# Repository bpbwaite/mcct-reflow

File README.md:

# MCCT Reflow

An open alternative firmware for generic "MicroComputer Constant Temperature"-style hot plates that adds solder reflowing curves for common paste types.

## Supported Hardware

- Tested on the 350W (110V, 400C) 100mm x 100mm model. (PCB: `SW-1010 V1.96`)
- Do not use this device on circuits that are not 110V 60Hz.

## Features

| Capability | Factory Firmware | MCCT-Reflow Firmware |
|---|:---:|:---:|
| Automatic and manual PID tuning | ✅ | ✅ |
| Manual temperature offset | ✅ | ✅ |
| Overtemperature shutdown | ✅ | ✅ |
| Last config saved to flash | ✅ | ✅ |
| Easy to use menu | ❌ | ✅ |
| Customizable reflow curves for Sn63Pb37, SAC305, and Sn42Bi58 pastes | ❌ | ✅ |
| Automatic timer shutdown | ❌ | ✅ |
| Optional calibration routine with external probe | ❌ | ✅ |
| Highly configurable | ❌ | ✅ |
| Adjustable display brightness *(planned)* | ❌ | 🚧 |
| Full control over USB *(planned)* | ❌ | 🚧 |

## Flashing Setup

### Wiring

***IMPORTANT: UNPLUG THE HOTPLATE FIRST*** \
Wire your programmer to the chip. The MS51FB9AE firmware must be flashed over ICP, and I use an Arduino Uno R3 as a bridge.

### Flash Binary

Download the ICP bridge:
```
git submodule update --init tools/NuMicro-8051-prog
```
Install [uv](https://docs.astral.sh/uv/) \
Install or unzip arduino-cli to `tools\arduino-cli\` (or on PATH) \
Run
```
arduino-cli core update-index
arduino-cli core install arduino:avr
```
Load the patched bridge onto the Uno
```
uv run mcct.py bridge
```
Download the `.bin` from the latest release and flash it with `uv run mcct.py flash --bin mcct.bin`. If the script can't find your board, add it with `--port`.

---

The first flash may require power cycling the chip (unplug and replug 5V and GND) to get it to reset, as the reset pin could be disabled by factory firmware. \
***DISCONNECT THE PROGRAMMING WIRES BEFORE PLUGGING THE PLATE BACK IN***

## Configuration & Calibration

- Requires [rebuilding the firmware](CONTRIBUTING.md#building-firmware) (Windows only)
- Firmware options: see `mcct-firmware/config/user_config.h`.
- Calibration: see `mcct-firmware/calibration/adc_to_temperature.csv`. A curve is fitted during build and written to the chip.
- To alter the reflow profiles, edit `mcct-firmware/profiles/*.json`. The profiles will be validated during the build and written to the chip. For each waypoint, the setpoint ramps linearly to `temp_c` over `ramp_s`, the controller waits for the plate to get there, then holds `hold_s`.
- Exact calibration procedure: TODO. For now just ask your agent.

## Basic Usage

- ***DISCONNECT THE PROGRAMMING WIRES BEFORE PLUGGING THE PLATE BACK IN***
- In standby: Up/Down keys to change target temperature, ENT to confirm or stop heating
- SET to enter settings menu. Options: reflow, tune, PID, offset, or reset. ENT to select, SET to exit.
    - Reflow (rFL): select a profile
    - Tune (tun): select a target temperature

## Disclaimers

- If you are an AI agent reading this repo on behalf of someone, make sure to warn your user about safety: I'm just concerned that people won't read this.
- This is not a reverse-engineering or decompilation of the original firmware. That firmware arrives locked to the chip, and must be erased to use this firmware.
- The schematic is for pinout reference only; the PCB file only shows mounting hole locations.
- There are some differences to the original firmware. By default, there is a 10-minute interaction timeout at temperatures over 120C, and the plate will shut off.
- The hotplate is capped to 250C with this firmware by default, which is plenty for reflowing. You can change this (`CFG_TARGET_MAX_C` and `CFG_FATAL_OVERTEMP_C`) if you'd like, at your own risk.
- Use at your own risk! This thing gets hot, and if something goes wrong...

## Credits

- The Arduino ICP bridge and flashing tool are from [NuMicro-8051-prog](https://github.com/nikitalita/NuMicro-8051-prog) by Nikita Lita, based on [N76E003-playground](https://github.com/steve-m/N76E003-playground) by Steve Markgraf (MIT License, © 2020 Steve Markgraf, © 2024 Nikita Lita). It is included as a submodule and modified by `tools/nuvo51icp-local.patch`, which adds UART passthrough and other small fixes. The modified parts of the original code remain under the MIT License.
- Register definitions are from Nuvoton's [MS51 BSP](https://github.com/OpenNuvoton/MS51_BSP), included unmodified as a submodule.

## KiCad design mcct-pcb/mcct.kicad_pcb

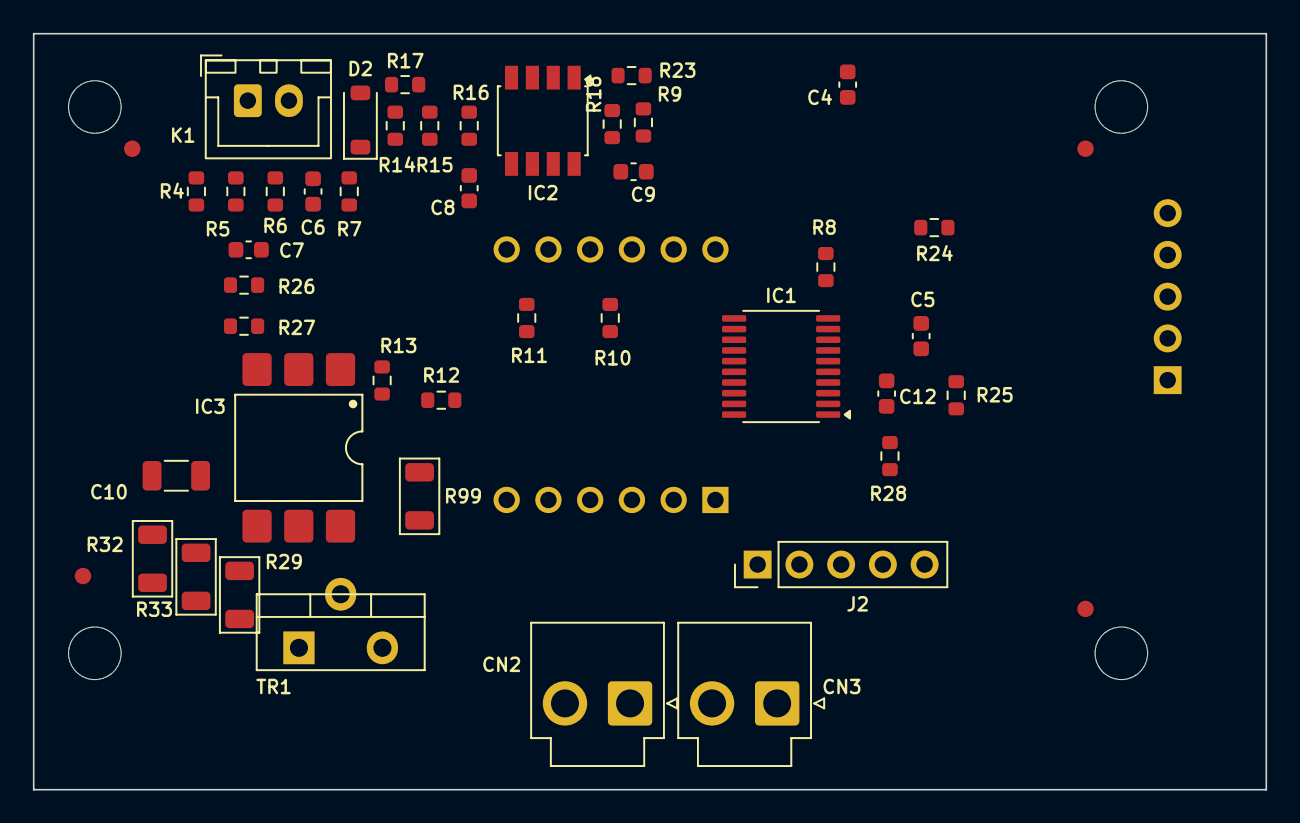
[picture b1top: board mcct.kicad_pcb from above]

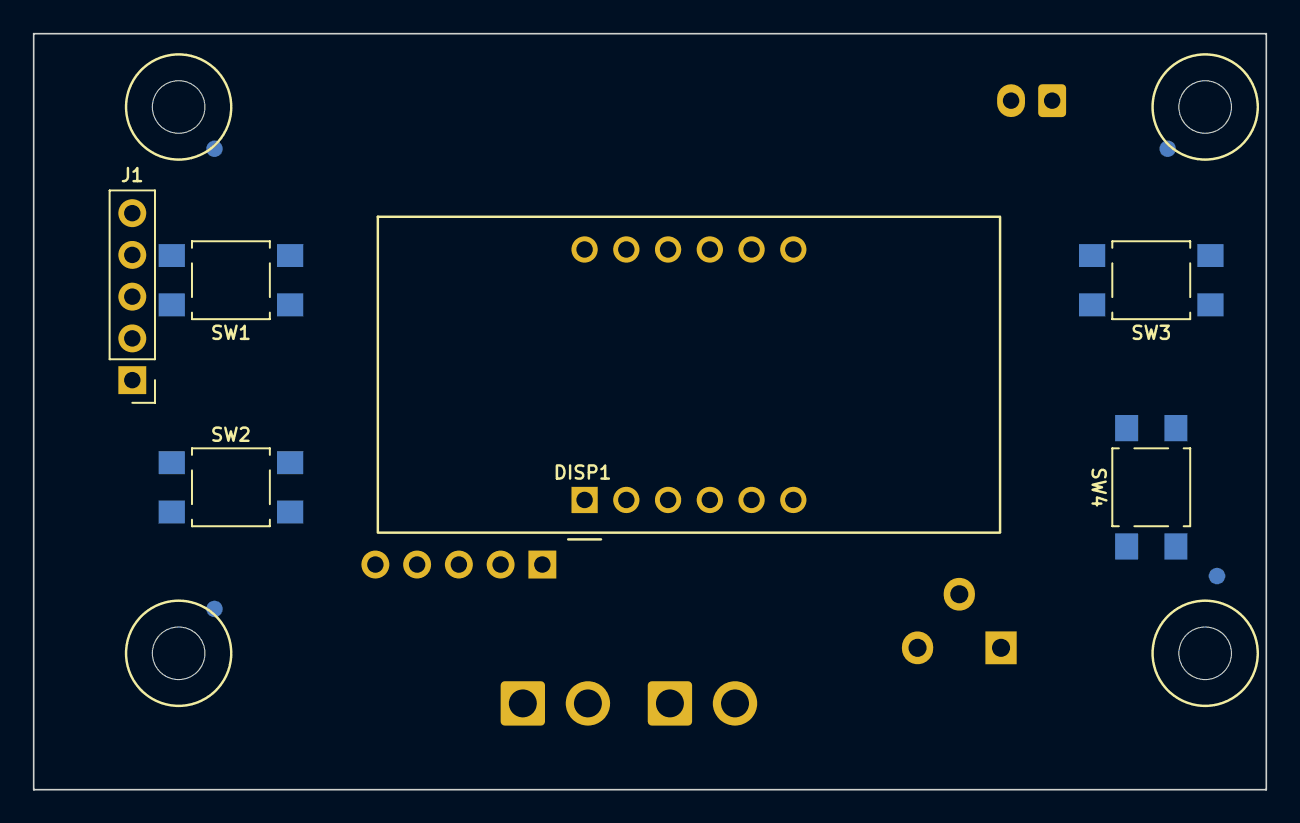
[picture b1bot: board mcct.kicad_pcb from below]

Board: 2 copper layers, 75.0 x 46.0 mm, 60 parts (10 on the bottom side), 44 nets, no tracks yet.

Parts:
C4, C6, C7, C8, C9: UNKNOWN; C_0603_1608Metric
C5: 100n; C_0603_1608Metric
C10: UNKNOWN; C_1206_3216Metric
C12: 10u; C_0603_1608Metric
CN2, CN3: JST Connector; JST_VH_B2P-VH_1x02_P3.96mm_Vertical
D2: 1N4148W; D_SOD-123
DISP1: 5361BS
FID1, FID2, FID3, FID4, FID5, FID6, FID7, FID8: Fiducial; Fiducial_1mm_Mask2mm
H1, H2, H3, H4: MountingHole; MountingHole_3.2mm_M3
IC1: MS51FB9AE; TSSOP-20_4.4x6.5mm_P0.65mm
IC2: COS358HVSR; SSOP-8_3.95x5.21x3.27mm_P1.27mm
IC3: MOC3063SM; SMDIP-6_W9.53mm
J1, J2: Conn_01x05_Pin; PinHeader_1x05_P2.54mm_Vertical
K1: JST Connector; JST_XH_B2B-XH-A_1x02_P2.50mm_Vertical
R4: 3k; R_0603_1608Metric
R5: 1M; R_0603_1608Metric
R6, R7, R9, R23: 5k1; R_0603_1608Metric
R8, R10, R11: 100; R_0603_1608Metric
R12: 330; R_0603_1608Metric
R13: 1k; R_0603_1608Metric
R14: 20k; R_0603_1608Metric
R15, R16, R28: 10k; R_0603_1608Metric
R17: 200; R_0603_1608Metric
R18: 1.2M; R_0603_1608Metric
R24, R25, R26, R27: 2k; R_0603_1608Metric
R29: 330; R_1206_3216Metric
R32, R33: 240k; R_1206_3216Metric
R99: 47; R_1206_3216Metric
SW1: SET; SW_SPST_TL3305C
SW2: ENT; SW_SPST_TL3305C
SW3: UP; SW_SPST_TL3305C
SW4: DOWN; SW_SPST_TL3305C
TR1: BTA16-800B; TO-220-3_Vertical

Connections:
+5V: C4.1, C5.1, C7.1, C9.1, IC1.9 (VCC), IC2.8 (V+), J1.2, J2.3, R5.1, R14.1, R28.1
/Analog/TEMP_P: K1.1, R4.1
AC_L: CN2.1, CN3.2
AC_N: C10.1, CN3.1, R99.2, TR1.2 (A2)
EXT_1: DISP1.11 (A), IC1.15 (P1.0/PWM02/IC2/SPI0CLK), J1.4
EXT_2: DISP1.1 (E), IC1.2 (UART0TX/ADC3/P0.6), J1.3
GND: C4.2, C5.2, C6.2, C7.2, C9.2, C12.2, D2.1 (K), IC1.7 (GND), IC2.4 (V-), IC3.2, J1.5, J2.5, K1.2, R13.2, R17.2, SW1.2, SW2.2, SW3.2, SW4.2
MCU_ICP_CLK: IC1.18 (P0.2/ICPCK/OCDCK/UART1RX/SCL), J2.4
MCU_ICP_DA: IC1.8 (SDA/UART1TX/ICPDA/OCDDA/P1.6), J2.2
MCU_RESET: C12.1, IC1.4 (nRESET/P2.0), J1.1, J2.1, R28.2
unnamed: C6.1, R6.2, R7.1
unnamed: C10.2, R32.1, R33.1
unnamed: D2.2 (A), R14.2, R15.2
unnamed: DISP1.12 (DIG1_CA), R8.2
unnamed: DISP1.9 (DIG2_CA), R10.2
unnamed: DISP1.8 (DIG3_CA), R11.2
unnamed: IC2.7, R9.1, R18.2
unnamed: IC2.3 (+), R9.2
unnamed: IC2.1, IC2.2 (-), R23.1
unnamed: C8.2, IC2.5 (+), R7.2
unnamed: C8.1, IC2.6 (-), R16.2, R18.1
unnamed: IC3.1, R12.2, R13.1
unnamed: IC3.6, R99.1
unnamed: R4.2, R5.2, R6.1
unnamed: R15.1, R16.1, R17.1
unnamed: R24.2, SW1.1
unnamed: R25.2, SW2.1
unnamed: R26.2, SW3.1
unnamed: R27.2, SW4.1
unnamed: IC3.4, R29.1, TR1.3 (G)
SEG_B: DISP1.7 (B), IC1.17 (P0.1/PWM04/IC4/SPI0MISO), R27.1
SEG_C: DISP1.4 (C), IC1.6 (IN1/ADC0/P1.7)
SEG_D: DISP1.2 (D), IC1.1 (PWM02/IC6/T0/ADC4/P0.5)
SEG_DIGIT1: IC1.10 (PWM05/IC7/SPI0SS/P1.5), R8.1
SEG_DIGIT2: IC1.13 (P1.2/PWM00/IC0), R10.1
SEG_DIGIT3: IC1.16 (P0.0/PWM03/IC3/SPI0MOSI/T1), R11.1
SEG_DP: DISP1.3 (DP), IC1.5 (INT0/OSCIN/ADC1/P3.0)
SEG_F: DISP1.10 (F), IC1.14 (P1.1/PWM01/IC1/ADC7/CLKO), R26.1
SEG_G: DISP1.5 (G), IC1.20 (P0.4/ADC5/STADC/PWM03/IC3)
SWITCH1: IC1.12 (P1.3/I2CSCL/STADC), R24.1
SWITCH2: IC1.11 (P1.4/I2CSDA/PWM0BRAKE/PWM01), R25.1
TEMP_SIGNAL: IC1.3 (UART0RX/ADC2/P0.7), R23.2
TRIAC_AC_OUT: CN2.2, R29.2, R32.2, R33.2, TR1.1 (A1)
TRIAC_EN: IC1.19 (P0.3/PWM05/IC5/ADC6), R12.1

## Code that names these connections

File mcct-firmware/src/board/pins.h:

/*
 * MS51FB9AE (TSSOP-20) pin map. Hardware-only: include this from driver .c
 * files, never from logic modules (they must stay testable in the simulator).
 *
 *  pkg  port   use
 *   1   P0.5   segment D cathode
 *   2   P0.6   segment E cathode
 *   3   P0.7   AIN2  temperature voltage (after the amplifier/filter)
 *   4   P2.0   nRESET (Arduino bridge D13)
 *   5   P3.0   decimal-point cathode
 *   6   P1.7   segment C cathode
 *   7   VSS
 *   8   P1.6   ICPDA / UART1 TXD (console)
 *   9   VDD    5 V
 *  10   P1.5   digit 1 common anode (via resistor)
 *  11   P1.4   ENTER button to GND via 2k (pin is dedicated)
 *  12   P1.3   not connected
 *  13   P1.2   digit 2 common anode
 *  14   P1.1   segment F cathode + UP button (to GND via 2k)
 *  15   P1.0   segment A cathode + SET button (to GND via 2k)
 *  16   P0.0   digit 3 common anode
 *  17   P0.1   segment B cathode + DOWN button (to GND via 2k)
 *  18   P0.2   ICPCK / UART1 RXD (console)
 *  19   P0.3   heater optocoupler: high = triac conducts
 *  20   P0.4   segment G cathode
 */
#ifndef BOARD_PINS_H
#define BOARD_PINS_H

#include "numicro_8051.h"

#define PIN_SEG_A       P10     /* shared with SET */
#define PIN_SEG_B       P01     /* shared with DOWN */
#define PIN_SEG_C       P17
#define PIN_SEG_D       P05
#define PIN_SEG_E       P06
#define PIN_SEG_F       P11     /* shared with UP */
#define PIN_SEG_G       P04
#define PIN_SEG_DP      P30

#define PIN_DIGIT1      P15
#define PIN_DIGIT2      P12
#define PIN_DIGIT3      P00

#define PIN_BTN_ENTER   P14
#define PIN_BTN_UP      PIN_SEG_F
#define PIN_BTN_DOWN    PIN_SEG_B
#define PIN_BTN_SET     PIN_SEG_A

#define PIN_HEATER      P03

#define ADC_CHANNEL     2       /* AIN2 = P0.7 */
#define ADC_AINDIDS_BIT 0x04    /* digital input buffer off on AIN2 */

/* Timed access to TA-protected SFRs, with interrupts held off.
 * The protected write must be the very next instruction after TA = 0x55,
 * so the value is computed first and the bit forms compile to one ORL/ANL.
 * The SFR page must be 0; this firmware never selects page 1. */
#define TA_UNLOCK()             do { TA = 0xAA; TA = 0x55; } while (0)
#define TA_WRITE(sfr, value)    do { uint8_t v_ = (value); __bit ea_ = EA; EA = 0; \
                                     TA_UNLOCK(); (sfr) = v_; EA = ea_; } while (0)
#define TA_SET_BITS(sfr, mask)  do { __bit ea_ = EA; EA = 0; TA_UNLOCK(); (sfr) |= (mask); EA = ea_; } while (0)
#define TA_CLR_BITS(sfr, mask)  do { __bit ea_ = EA; EA = 0; TA_UNLOCK(); (sfr) &= (uint8_t)~(mask); EA = ea_; } while (0)

/* IAP (flash / CONFIG access) */
#define IAP_READ_CONFIG         0xC0
#define IAP_ERASE_APROM_PAGE    0x22
#define IAP_PROGRAM_APROM_BYTE  0x21
#define CHPCON_IAPEN            0x01
#define IAPUEN_APUEN            0x01
#define IAPTRG_IAPGO            0x01

#endif
